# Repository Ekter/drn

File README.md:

# drn

drone controller using ftprci

See docs/R&D Rapport Final.pdf for more information

[The other repo is here](https://github.com/jaimealbapastor/Drone-Camera-Control)

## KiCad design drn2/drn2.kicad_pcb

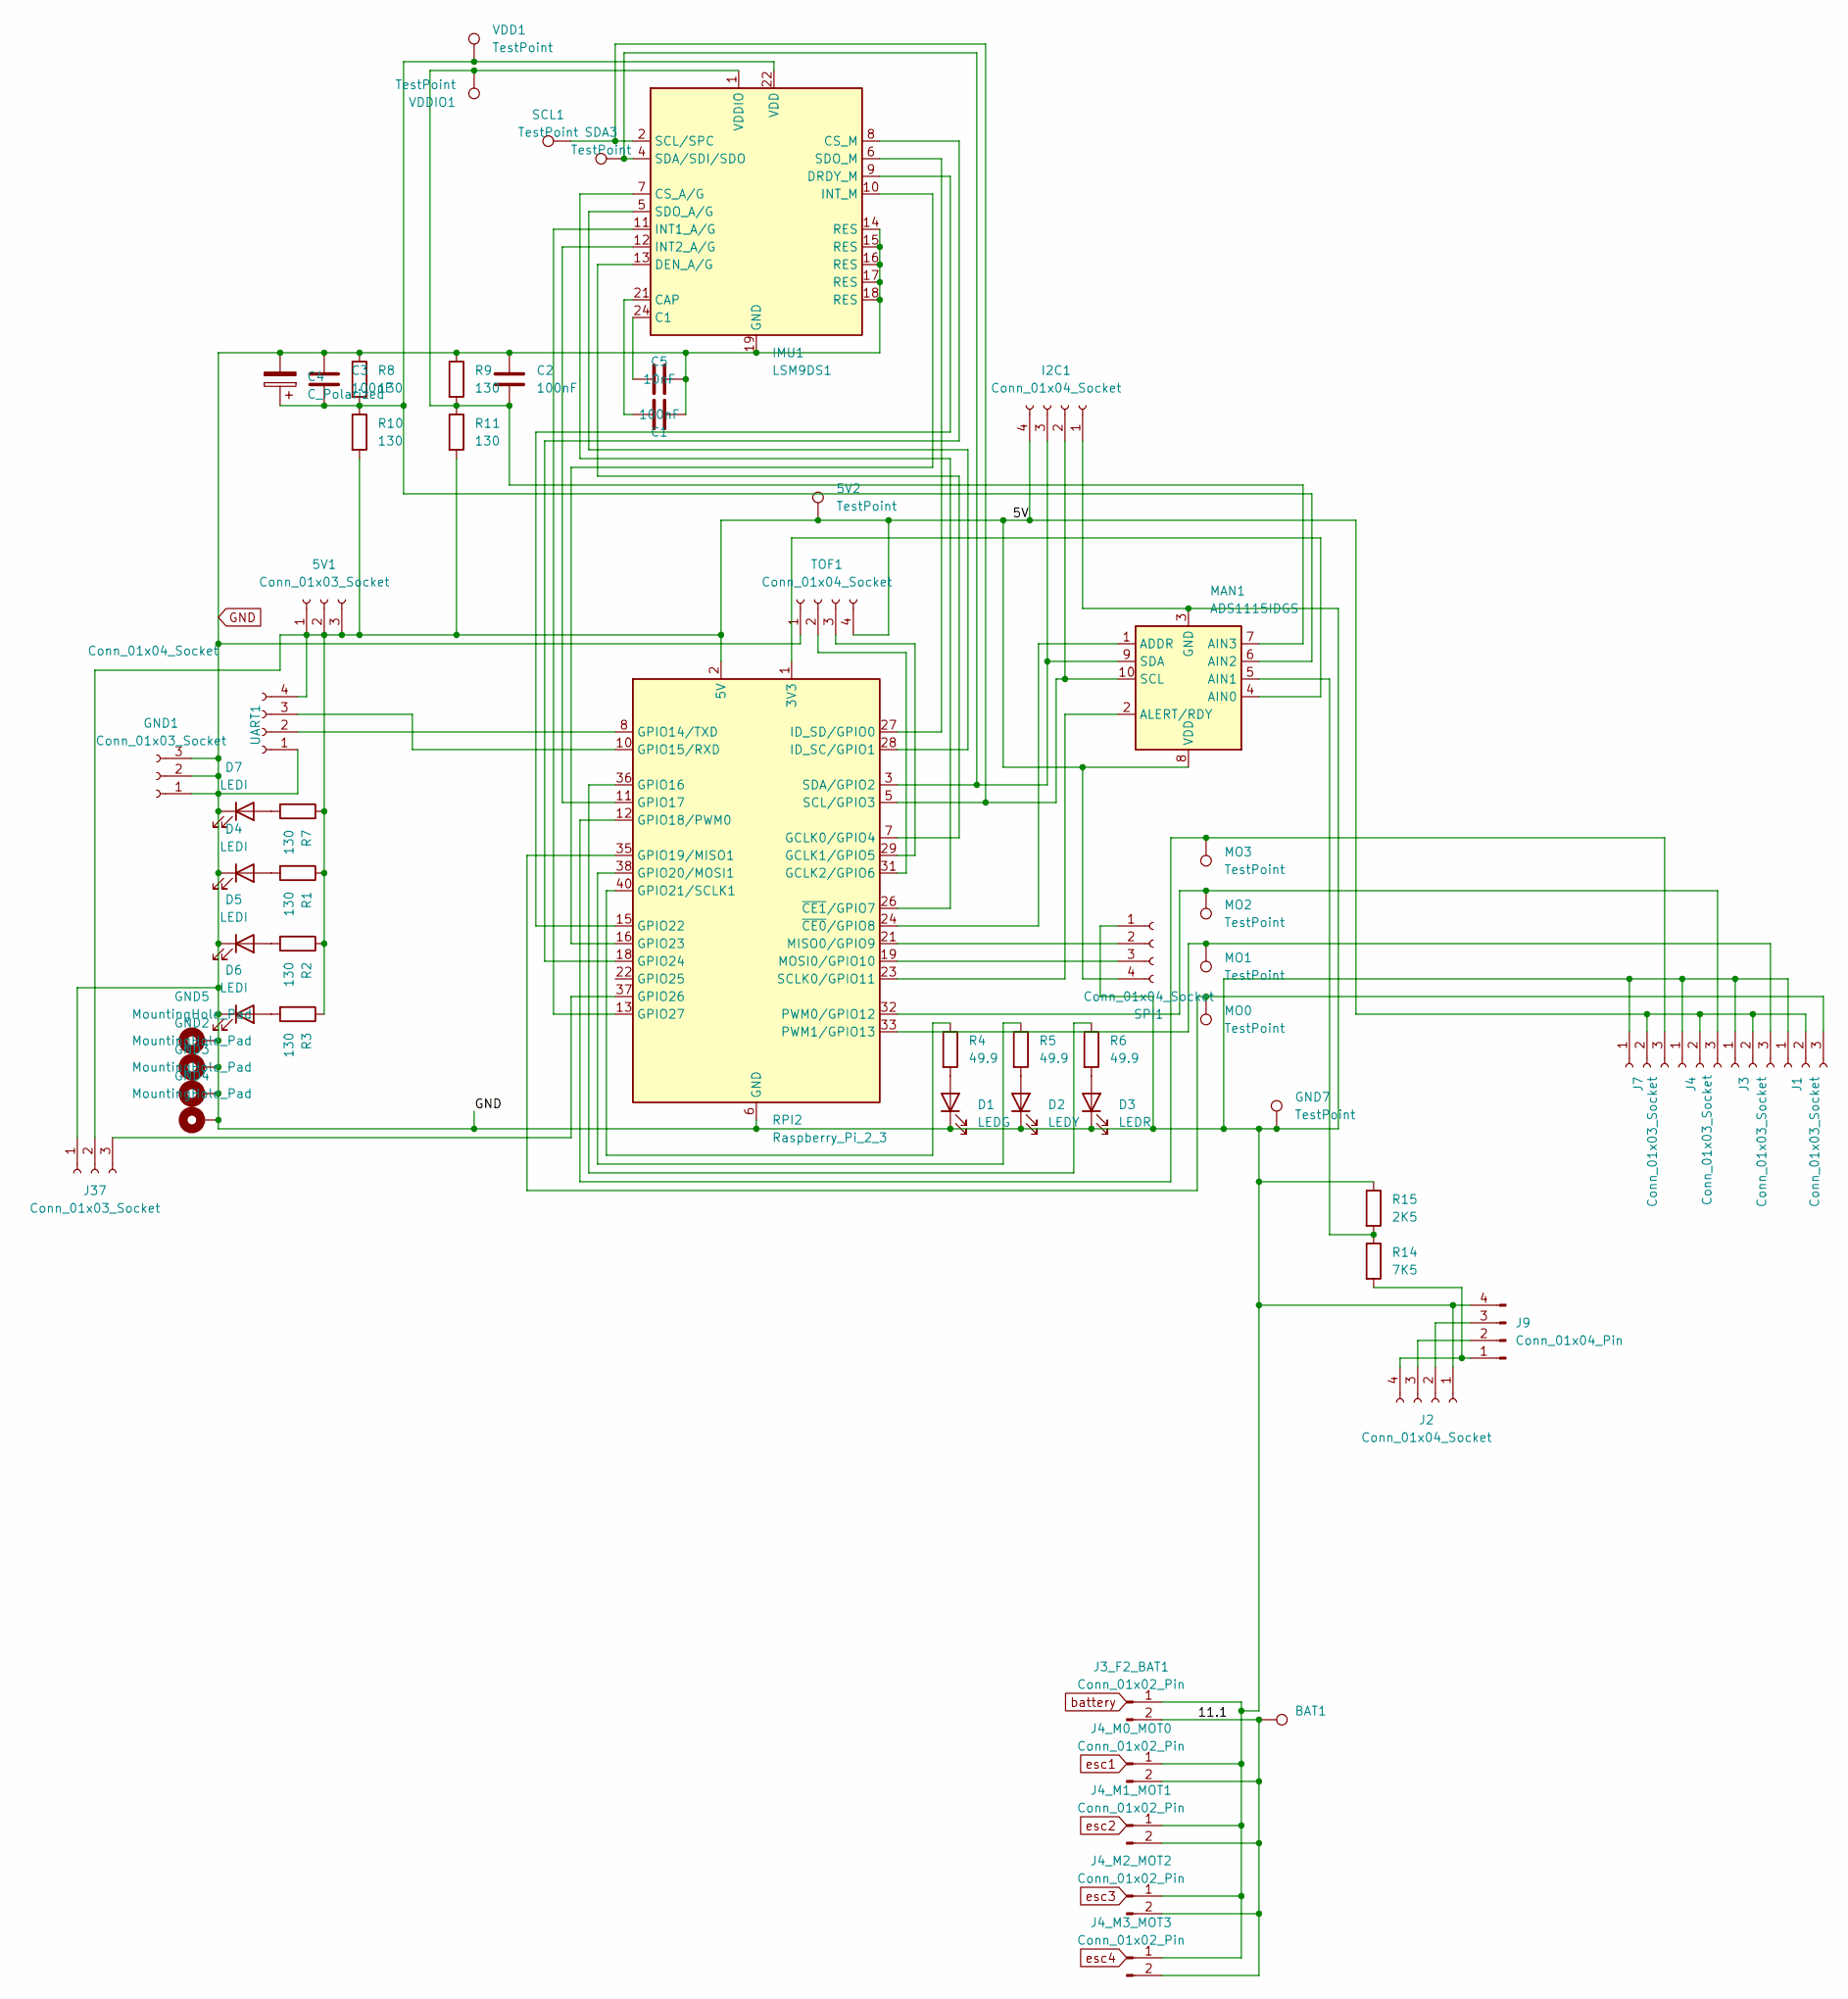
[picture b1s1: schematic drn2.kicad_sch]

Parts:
5V1: Conn_01x03_Socket; PinHeader_1x03_P2.54mm_Vertical; LCSC Part C541850
5V2: TestPoint; TestPoint_Pad_D1.0mm; JLCPCB BOM 0
BAT1: TestPoint; TestPoint_Pad_D1.0mm; JLCPCB BOM 0
C1, C2, C3: 100nF; C_0603_1608Metric_Pad1.08x0.95mm_HandSolder; LCSC Part C66501
C4: C_Polarized; CP_Elec_4x5.4; LCSC Part C72483
C5: 10nF; C_0603_1608Metric_Pad1.08x0.95mm_HandSolder; LCSC Part C519406
D1: LEDG; LED_0603_1608Metric; LCSC Part C965806
D2: LEDY; LED_0603_1608Metric; LCSC Part C965802
D3: LEDR; LED_0603_1608Metric; LCSC Part C965798
D4, D5, D6, D7: LEDI; LED_0603_1608Metric; LCSC Part C412284
GND1: Conn_01x03_Socket; PinHeader_1x03_P2.54mm_Vertical; LCSC Part C541850
GND2, GND3, GND4, GND5: MountingHole_Pad; MountingHole_3.2mm_M3_Pad_Via; JLCPCB BOM 0
GND7: TestPoint; TestPoint_Pad_D1.0mm; JLCPCB BOM 0
I2C1: Conn_01x04_Socket; PinHeader_1x04_P2.54mm_Vertical; JLCPCB BOM 1
IMU1: LSM9DS1; LGA-24L_3x3.5mm_P0.43mm; LCSC Part C2655096
J1, J3, J4, J7: Conn_01x03_Socket; PinHeader_1x03_P2.54mm_Vertical; LCSC Part C49257
J2: Conn_01x04_Socket; PinSocket_1x04_P2.54mm_Vertical; LCSC Part C2718488
J3_F2_BAT1: Conn_01x02_Pin; AMASS_XT60-F_1x02_P7.20mm_Vertical; LCSC Part C98733
J4_M0_MOT0, J4_M1_MOT1, J4_M2_MOT2, J4_M3_MOT3: Conn_01x02_Pin; AMASS_XT60-F_1x02_P7.20mm_Vertical; LCSC Part C98734
J9: Conn_01x04_Pin; JST_XH_B4B-XH-A_1x04_P2.50mm_Vertical; LCSC Part C18077835
J37: Conn_01x03_Socket; PinHeader_1x03_P2.54mm_Vertical; LCSC Part C541850
MAN1: ADS1115IDGS; TSSOP-10_3x3mm_P0.5mm; LCSC Part C37593
MO0, MO1, MO2, MO3: TestPoint; TestPoint_Pad_D1.0mm; JLCPCB BOM 0
R1, R2, R3, R7, R8, R9, R10, R11: 130; R_0603_1608Metric; LCSC Part C22796
R4, R5, R6: 49.9; R_0603_1608Metric; LCSC Part C23185
R14: 7K5; R_0603_1608Metric; LCSC Part C728597
R15: 2K5; R_0603_1608Metric; LCSC Part C304065
RPI2: Raspberry_Pi_2_3; Raspberry_Pi_Zero_Socketed_THT_FaceDown_MountingHoles; JLCPCB BOM 1
SCL1: TestPoint; TestPoint_Pad_D1.0mm; JLCPCB BOM 0
SDA3: TestPoint; TestPoint_Pad_D1.0mm; JLCPCB BOM 0
SPI1: Conn_01x04_Socket; PinHeader_1x04_P2.54mm_Vertical; JLCPCB BOM 1
TOF1: Conn_01x04_Socket; PinHeader_1x04_P2.54mm_Vertical; JLCPCB BOM 0
UART1: Conn_01x04_Socket; PinHeader_1x04_P2.54mm_Vertical; JLCPCB BOM 1
VDD1: TestPoint; TestPoint_Pad_D1.0mm; JLCPCB BOM 0
VDDIO1: TestPoint; TestPoint_Pad_D1.0mm; JLCPCB BOM 0

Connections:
/5V: 5V1.1, 5V1.2, 5V1.3, 5V2.1, I2C1.4, J1.2, J3.2, J4.2, J7.2, J37.2, MAN1.8 (VDD), R1.1, R2.1, R3.1, R7.1, R10.2, R11.2, RPI2.2 (5V), RPI2.4 (5V), SPI1.4, TOF1.4, UART1.4
/11.1: BAT1.1, J3_F2_BAT1.2, J4_M0_MOT0.2, J4_M1_MOT1.2, J4_M2_MOT2.2, J4_M3_MOT3.2
GND: C1.1, C2.1, C3.1, C4.2, C5.1, D1.1 (K), D2.1 (K), D3.1 (K), D4.1 (K), D5.1 (K), D6.1 (K), D7.1 (K), GND1.1, GND1.2, GND1.3, GND2.1, GND3.1, GND4.1, GND5.1, GND7.1, I2C1.1, IMU1.14 (RES), IMU1.15 (RES), IMU1.16 (RES), IMU1.17 (RES), IMU1.18 (RES), IMU1.19 (GND), IMU1.20 (GND), J1.1, J2.1, J3.1, J3_F2_BAT1.1, J4.1, J4_M0_MOT0.1, J4_M1_MOT1.1, J4_M2_MOT2.1, J4_M3_MOT3.1, J7.1, J9.4, J37.1, MAN1.3 (GND), R8.1, R9.1, R15.1, RPI2.6 (GND), RPI2.9 (GND), RPI2.14 (GND), RPI2.20 (GND), RPI2.25 (GND), RPI2.30 (GND), RPI2.34 (GND), RPI2.39 (GND), SPI1.1, TOF1.1, UART1.1
unnamed: D1.2 (A), R4.2
unnamed: D2.2 (A), R5.2
unnamed: D3.2 (A), R6.2
unnamed: D4.2 (A), R1.2
unnamed: D5.2 (A), R2.2
unnamed: D6.2 (A), R3.2
unnamed: D7.2 (A), R7.2
unnamed: I2C1.2, IMU1.2 (SCL/SPC), MAN1.10 (SCL), RPI2.5 (SCL/GPIO3), SCL1.1
unnamed: I2C1.3, IMU1.4 (SDA/SDI/SDO), MAN1.9 (SDA), RPI2.3 (SDA/GPIO2), SDA3.1
unnamed: C1.2, IMU1.24 (C1)
unnamed: C5.2, IMU1.21 (CAP)
unnamed: IMU1.7 (CS_A/G), RPI2.26 (~CE1/GPIO7)
unnamed: IMU1.8 (CS_M), RPI2.18 (GPIO24)
unnamed: IMU1.13 (DEN_A/G), RPI2.7 (GCLK0/GPIO4)
unnamed: IMU1.9 (DRDY_M), RPI2.15 (GPIO22)
unnamed: IMU1.11 (INT1_A/G), RPI2.13 (GPIO27)
unnamed: IMU1.12 (INT2_A/G), RPI2.11 (GPIO17)
unnamed: IMU1.10 (INT_M), RPI2.16 (GPIO23)
unnamed: IMU1.5 (SDO_A/G), RPI2.28 (ID_SC/GPIO1)
unnamed: IMU1.6 (SDO_M), RPI2.27 (ID_SD/GPIO0)
unnamed: J1.3, MO0.1, RPI2.35 (GPIO19/MISO1)
unnamed: J2.2, J9.3
unnamed: J2.3, J9.2
unnamed: J2.4, J9.1, R14.2
unnamed: J3.3, MO1.1, RPI2.33 (PWM1/GPIO13)
unnamed: J4.3, MO2.1, RPI2.32 (PWM0/GPIO12)
unnamed: J7.3, MO3.1, RPI2.12 (GPIO18/PWM0)
unnamed: J37.3, RPI2.37 (GPIO26)
unnamed: MAN1.1 (ADDR), RPI2.24 (~CE0/GPIO8)
unnamed: MAN1.4 (AIN0), RPI2.1 (3V3), RPI2.17 (3V3)
unnamed: MAN1.5 (AIN1), R14.1, R15.2
unnamed: C3.2, C4.1, IMU1.22 (VDD), IMU1.23 (VDD), MAN1.6 (AIN2), R8.2, R10.1, VDD1.1
unnamed: C2.2, IMU1.1 (VDDIO), IMU1.3 (VDDIO), MAN1.7 (AIN3), R9.2, R11.1, VDDIO1.1
unnamed: MAN1.2 (ALERT/RDY), RPI2.23 (SCLK0/GPIO11)
unnamed: RPI2.29 (GCLK1/GPIO5), TOF1.3
unnamed: RPI2.31 (GCLK2/GPIO6), TOF1.2
unnamed: RPI2.8 (GPIO14/TXD), UART1.2
unnamed: RPI2.10 (GPIO15/RXD), UART1.3
unnamed: R6.1, RPI2.36 (GPIO16)
unnamed: R5.1, RPI2.38 (GPIO20/MOSI1)
unnamed: R4.1, RPI2.40 (GPIO21/SCLK1)
unnamed: RPI2.21 (MISO0/GPIO9), SPI1.2
unnamed: RPI2.19 (MOSI0/GPIO10), SPI1.3

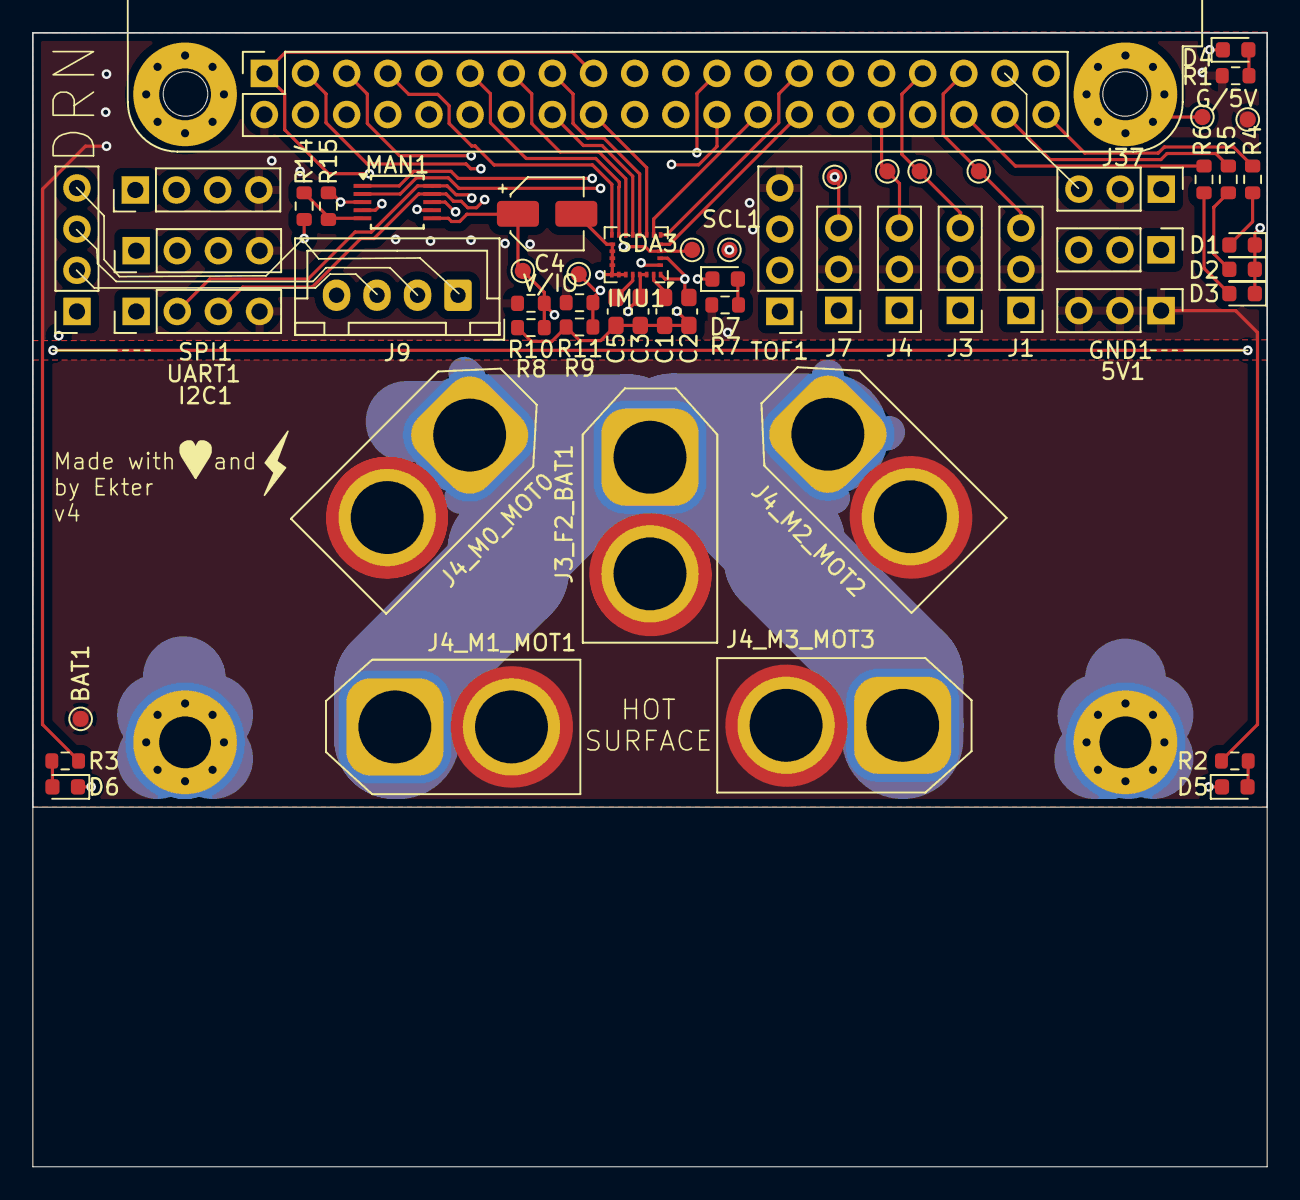
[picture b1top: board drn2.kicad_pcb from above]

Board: 4 copper layers, 76.2 x 70.0 mm, 61 parts (0 on the bottom side), 46 nets.

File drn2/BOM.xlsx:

Comment | Designator | Footprint | LCSC Part Number
Conn_01x03_Socket | 5V1 | PinHeader_1x03_P2.54mm_Vertical | C541850
100nF | C1,C2,C3 | C_0603_1608Metric_Pad1.08x0.95mm_HandSolder | C66501
C_Polarized | C4 | CP_Elec_4x5.4 | C72483
10nF | C5 | C_0603_1608Metric_Pad1.08x0.95mm_HandSolder | C519406
LEDG | D1 | LED_0603_1608Metric | C965806
LEDY | D2 | LED_0603_1608Metric | C965802
LEDR | D3 | LED_0603_1608Metric | C965798
LEDI | D4,D5,D6,D7 | LED_0603_1608Metric | C412284
Conn_01x03_Socket | GND1 | PinHeader_1x03_P2.54mm_Vertical | C541850
Conn_01x04_Socket | I2C1 | PinHeader_1x04_P2.54mm_Vertical | C2718488
LSM9DS1 | IMU1 | LGA-24L_3x3.5mm_P0.43mm | C2655096
Conn_01x03_Socket | J1,J3,J4,J7,J37 | PinHeader_1x03_P2.54mm_Vertical | C541850
Conn_01x04_Socket | J2 | PinSocket_1x04_P2.54mm_Vertical | C2718488
Conn_01x02_Pin | J3_F2_BAT1 | AMASS_XT60-F_1x02_P7.20mm_Vertical | C98733
Conn_01x02_Pin | J4_M0_MOT0 | AMASS_XT60-F_1x02_P7.20mm_Vertical | C98734
Conn_01x02_Pin | J4_M1_MOT1 | AMASS_XT60-F_1x02_P7.20mm_Vertical | C98734
Conn_01x02_Pin | J4_M2_MOT2 | AMASS_XT60-F_1x02_P7.20mm_Vertical | C98734
Conn_01x02_Pin | J4_M3_MOT3 | AMASS_XT60-F_1x02_P7.20mm_Vertical | C98734
Conn_01x04_Pin | J9 | JST_XH_B4B-XH-A_1x04_P2.50mm_Vertical | C18077835
ADS1115IDGS | MAN1 | TSSOP-10_3x3mm_P0.5mm | C37593
130 | R1,R2,R3,R7,R8,R9,R10,R11 | R_0603_1608Metric | C22796
49.9 | R4,R5,R6 | R_0603_1608Metric | C23185
7K5 | R14 | R_0603_1608Metric | C728597
2K5 | R15 | R_0603_1608Metric | C304065
Raspberry_Pi_2_3 | RPI2 | Raspberry_Pi_Zero_Socketed_THT_FaceDown_MountingHoles | C2977589
Conn_01x04_Socket | SPI1 | PinHeader_1x04_P2.54mm_Vertical | C2718488
Conn_01x04_Socket | UART1 | PinHeader_1x04_P2.54mm_Vertical | C2718488

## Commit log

2024-12-06 feat: pcb v2.5
2024-12-06 feat: pcb version 2.8
2024-12-07 feat: pcb v3
2025-01-04 feat: new pcb version, removed mess
2025-01-04 feat: removed kicad backups
2025-01-05 feat: requirements
2025-01-09 feat: turn on led at startup
2025-01-09 feat: change lsm pin to 1
2025-01-09 fix: typo on module
2025-01-09 fix: error in main loop print
2025-01-09 feat: change pin?
2025-01-09 feat: enable communication at startup
2025-01-09 feat: i2cdetect print
2025-01-09 feat: fix pin states
2025-01-09 feat: leds blinking
2025-01-09 feat: leds blinking p2
2025-01-09 fix: i2c address
2025-01-10 feat: reg6 lsm9ds1
2025-01-11 feat: ctrl regs review
2025-01-11 fix: format error
2025-01-11 fix: nicer display
2025-01-11 feat: nicer display with defaults
2025-01-11 fix: change access on regs acc gyro
2025-01-11 fix: match format of display and default regs
2025-01-13 feat: edit requirements
2025-01-13 feat: escs init
2025-01-13 feat: progression prints
2025-01-13 feat: light load test on propellers
2025-01-13 feat: stop program and correction to load test
2025-01-13 fix: order error in load test
2025-01-13 feat: longer load
2025-01-13 feat: 2 way init
2025-01-13 feat: 2-1-1 init
2025-01-18 feat: round esc init
2025-01-18 feat: failsafe for main
2025-01-18 feat: git pull in the test script
2025-01-18 made scripts executable as default
2025-01-18 feat: sensor check before motors
2025-01-18 main loop in try
2025-01-18 feat: disconnect esc at launch
2025-01-19 feat: disable mot19
2025-01-19 feat: disable test
2025-01-19 fix: remove duplicate settings
2025-01-19 feat: display current state of motors
2025-01-19 feat: testing loop on 12
2025-01-19 feat: change mean to match neutral point
2025-01-19 feat: correct range
2025-01-19 feat: test for 19
2025-01-19 feat: unified init for motors
2025-01-26 feat: drn pcb v3 almost done
2025-01-27 feat: final report other things like simulations and 3d models coming later
2025-01-27 docs: update readme
2025-02-06 drn v4
2025-02-07 v4 done, requires FP check
